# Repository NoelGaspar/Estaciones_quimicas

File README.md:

# Estaciones_químicas

Sistema de medicion de variables para análisis con aplicaciones químicas. El objetivo es desarrollar un sistema que permita medir variables químicas, (ej NO3-, F- y pH) en matraces con líquidos y muestras de suelos.

- Código realizado en Platformio
- Microcontrolador basado en Arduino Uno

## Sondas a integrar:
- Sensor pH x041800394 (Gravity - Analog Spear) https://www.dfrobot.com/product-1668.html
- Sensor Oxigeno Disuelto (Atlas scientific) 
- Sensor pH4502c
- Sensor Oxigeno discuelto dog2 - A0007 (Gravity)
- Nitrato NO3 (tipo serie 43) serie NO43 - A0001

## Requerimientos del sistema

- Microcnotrolador.
- Datalogger
- Tipo de comunicación
- Códigos que permitan calibración online.

## Dependencias
- ph_AO Analog   ph sensor gravity industrial
- DO_RX Software serial DO 
- DO_TX Software serial DO 
- ph_A1 Analog   ph sensor 
- DO_A2 Analog   DO sensor gravity
- ph_A3 Analog   ph sensor gravity lab
- phOPR_A4 Analog ph/opr sensor

## TODO

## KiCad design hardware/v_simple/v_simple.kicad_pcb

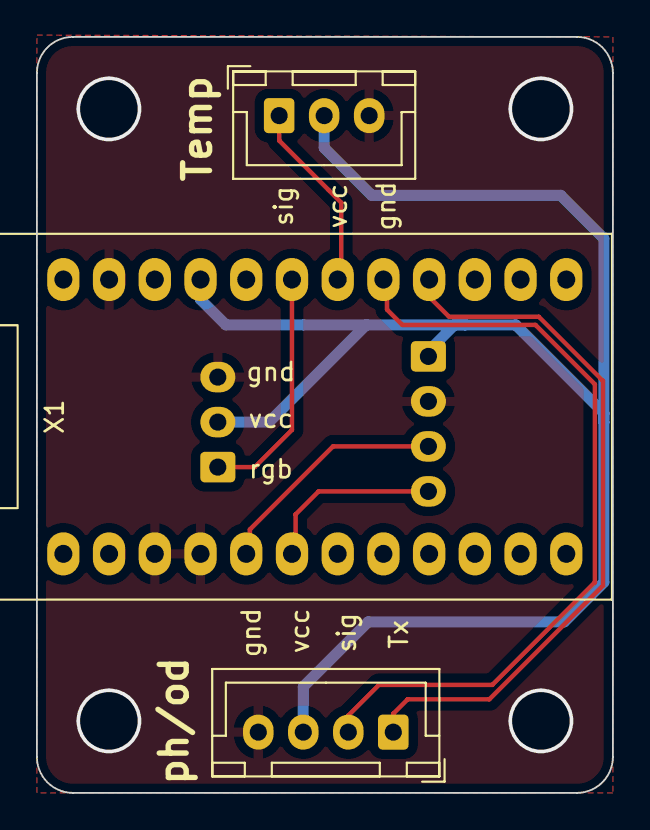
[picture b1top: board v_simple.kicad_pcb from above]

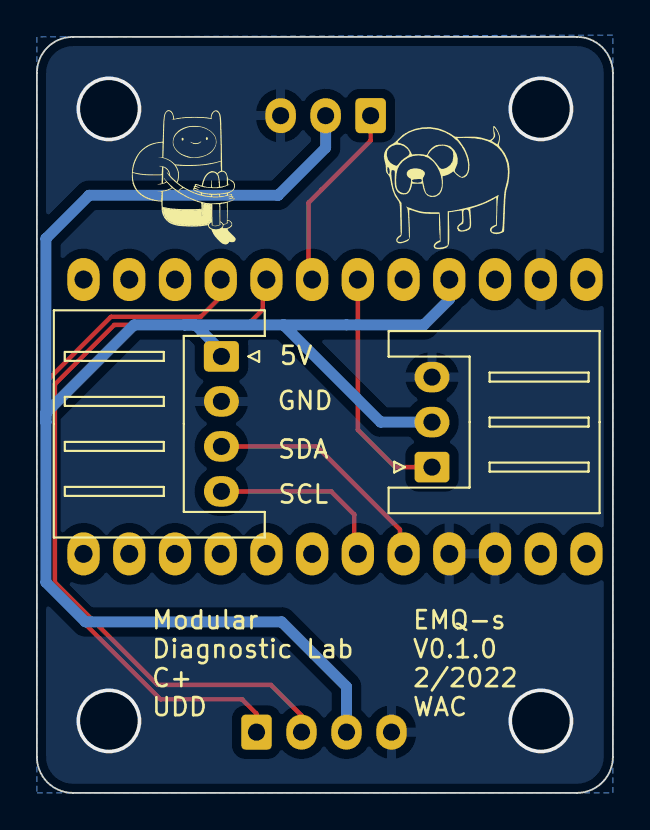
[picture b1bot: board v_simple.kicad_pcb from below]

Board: 2 copper layers, 32.0 x 42.0 mm, 5 parts (2 on the bottom side), 8 nets.

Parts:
J2: HDR-4x1; JST_XH_B4B-XH-A_1x04_P2.50mm_Vertical
J3: HDR-3x1; JST_XH_B3B-XH-A_1x03_P2.50mm_Vertical
J4: HDR-4x1; JST_XH_S4B-XH-A_1x04_P2.50mm_Horizontal
J6: HDR-3x1; JST_XH_S3B-XH-A_1x03_P2.50mm_Horizontal
X1: Arduino_pro_micro

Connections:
/GND: J2.4, J3.3, J4.2, J6.3, X1.3 (GND), X1.4 (GND), X1.23 (GND)
/RGB: J6.1, X1.19 (A2)
/SCL: J4.4, X1.6 (3)
/SDA: J4.3, X1.5 (2)
/SIG_Rx: J2.2, X1.17 (A0)
/SIG_TEMP: J3.1, X1.18 (A1)
/Tx: J2.1, X1.16 (15)
/VCC: J2.3, J3.2, J4.1, J6.2, X1.21 (VCC)

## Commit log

2021-12-23 adding first version of code
2022-02-07 adding fab files of board
2022-02-10 adding test board
2022-02-25 adding breakout for atlas do sensor
